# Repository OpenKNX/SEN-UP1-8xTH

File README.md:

# UP1-8xSensor
OpenKNX 8channel Temperature/Humidity Sensor

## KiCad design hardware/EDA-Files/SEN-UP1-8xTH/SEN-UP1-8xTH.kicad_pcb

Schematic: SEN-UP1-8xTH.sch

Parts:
J1: Conn_01x20; OpenKNX_UP1-PCBConnector_1x20_App_3D; LCSC C2334

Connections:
+3V3: J1.2; also elsewhere on the board
GND: J1.1; also elsewhere on the board
GPIO14: J1.5; also elsewhere on the board
GPIO15: J1.6; also elsewhere on the board
GPIO16: J1.7; also elsewhere on the board
GPIO17: J1.8; also elsewhere on the board
GPIO18: J1.9; also elsewhere on the board
GPIO19: J1.10; also elsewhere on the board
GPIO20: J1.11; also elsewhere on the board
GPIO21: J1.12; also elsewhere on the board
GPIO22: J1.13; also elsewhere on the board
GPIO23: J1.14; also elsewhere on the board
GPIO24: J1.15; also elsewhere on the board
GPIO25: J1.16; also elsewhere on the board
GPIO26: J1.17; also elsewhere on the board
GPIO27: J1.18; also elsewhere on the board
GPIO28: J1.19; also elsewhere on the board
GPIO29: J1.20; also elsewhere on the board
VCC2: J1.3

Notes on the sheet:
GP14: SPI1 SCK / UART0 CTS / I2C1 SDA / PWM7 A
GP15: SPI1 TX / UART0 RTS / I2C1 SCL / PWM7 B
GP18: SPI0 SCK / UART0 CTS / I2C1 SDA / PWM1 A
GP19: SPI0 TX / UART0 RTS / I2C1 SCL / PWM1 B
GP17: SPI0 CS / UART0 RX / I2C0 SCL / PWM0 B
GP16: SPI0 RX / UART0 TX / I2C0 SDA / PWM0 A
GP13: SPI1 CS / UART0 RX / I2C0 SCL / PWM6 B
GP20: SPI0 RX / UART1 TX / I2C0 SDA / PWM2 A
GP21: SPI0 CS / UART1 RX / I2C0 SCL / PWM2 B
GP22: SPI0 SCK / UART1 CTS / I2C1 SDA / PWM3 A
GP23: SPI0 SCK / UART1 RTS / I2C1 SCL / PWM3 B
GP24: SPI1 RX / UART1 TX / I2C0 SDA / PWM4 A
GP25: SPI1 CS / UART1 RX / I2C0 SCL / PWM4 B
GP26: SPI1 SCK / UART1 CTS / I2C1 SDA / PWM5 A / ADC0
GP27: SPI1 TX / UART1 RTS / I2C1 SCL / PWM5 B / ADC1
GP28: SPI1 RX / UART0 TX / I2C0 SDA / PWM6 A / ADC2
GP29: SPI1 CS / UART0 RX / I2C0 SCL / PWM6 B / ADC3
Vcc2 from BCU (5V)

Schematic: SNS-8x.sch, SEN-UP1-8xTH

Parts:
J2, J3: Conn_01x04; Cixi_Kefa_KF128-2.54-4p; LCSC C474922
J4, J5: Conn_01x05; Cixi_Kefa_KF128-2.54-5p
R1, R2, R3, R4, R5, R6, R7, R8, R9, R10, R11, R12, R13, R14, R15, R16: R; R_0805_2012Metric_Pad1.15x1.40mm_HandSolder
U1, U2, U3, U4, U5, U6, U7, U8: USBLC6-2SC6; SOT-23-6

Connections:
+3V3: J4.5, R1.1, R2.1, R3.1, R4.1, R5.1, R6.1, R7.1, R8.1, R9.1, R10.1, R11.1, R12.1, R13.1, R14.1, R15.1, R16.1, U1.5 (VBUS), U2.5 (VBUS), U3.5 (VBUS), U4.5 (VBUS), U5.5 (VBUS), U6.5 (VBUS), U7.5 (VBUS), U8.5 (VBUS); also elsewhere on the board
GND: J5.1, U1.2 (GND), U2.2 (GND), U3.2 (GND), U4.2 (GND), U5.2 (GND), U6.2 (GND), U7.2 (GND), U8.2 (GND); also elsewhere on the board
GPIO14: U8.3 (IO2); also elsewhere on the board
GPIO15: U8.1 (IO1); also elsewhere on the board
GPIO16: U7.3 (IO2); also elsewhere on the board
GPIO17: U7.1 (IO1); also elsewhere on the board
GPIO18: U6.3 (IO2); also elsewhere on the board
GPIO19: U6.1 (IO1); also elsewhere on the board
GPIO20: U5.3 (IO2); also elsewhere on the board
GPIO21: U5.1 (IO1); also elsewhere on the board
GPIO22: U4.3 (IO2); also elsewhere on the board
GPIO23: U4.1 (IO1); also elsewhere on the board
GPIO24: U3.3 (IO2); also elsewhere on the board
GPIO25: U3.1 (IO1); also elsewhere on the board
GPIO26: U2.3 (IO2); also elsewhere on the board
GPIO27: U2.1 (IO1); also elsewhere on the board
GPIO28: U1.3 (IO2); also elsewhere on the board
GPIO29: U1.1 (IO1); also elsewhere on the board
SCL0_A_P: J2.1, R16.2, U1.6 (IO1)
SCL0_C_P: J4.1, R12.2, U3.6 (IO1)
SCL0_E_P: J5.2, R8.2, U5.6 (IO1)
SCL0_G_P: J3.1, R4.2, U7.6 (IO1)
SCL1_B_P: J2.3, R14.2, U2.6 (IO1)
SCL1_D_P: J4.3, R10.2, U4.6 (IO1)
SCL1_F_P: J5.4, R6.2, U6.6 (IO1)
SCL1_H_P: J3.3, R2.2, U8.6 (IO1)
SDA0_A_P: J2.2, R15.2, U1.4 (IO2)
SDA0_C_P: J4.2, R11.2, U3.4 (IO2)
SDA0_E_P: J5.3, R7.2, U5.4 (IO2)
SDA0_G_P: J3.2, R3.2, U7.4 (IO2)
SDA1_B_P: J2.4, R13.2, U2.4 (IO2)
SDA1_D_P: J4.4, R9.2, U4.4 (IO2)
SDA1_F_P: J5.5, R5.2, U6.4 (IO2)
SDA1_H_P: J3.4, R1.2, U8.4 (IO2)

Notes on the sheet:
Sensor (SHT31, BME280, ...)

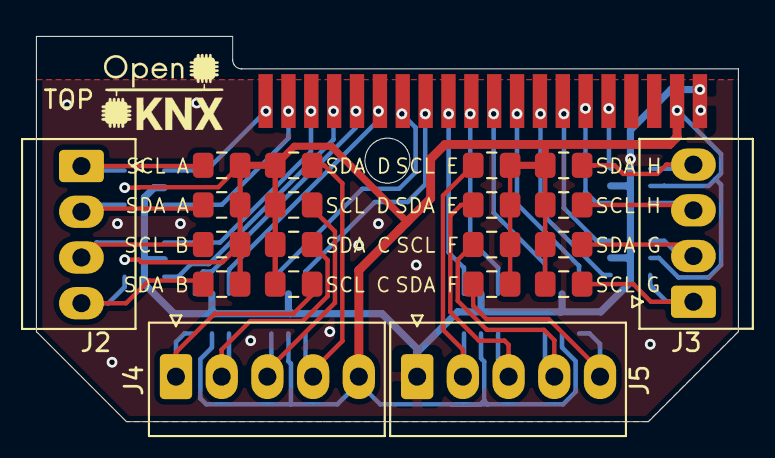
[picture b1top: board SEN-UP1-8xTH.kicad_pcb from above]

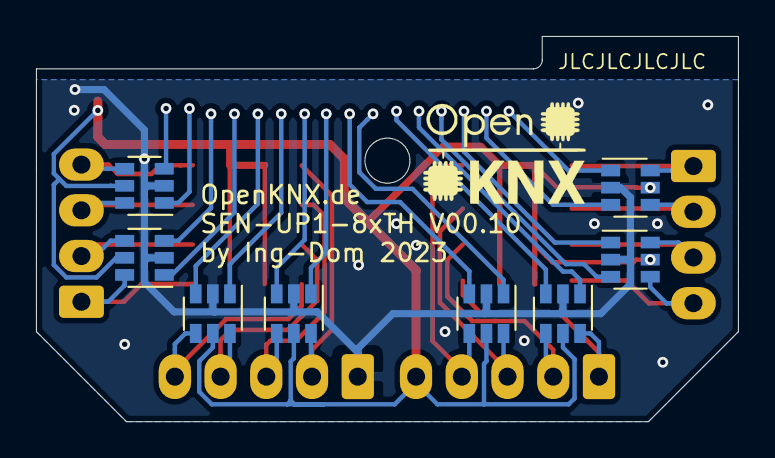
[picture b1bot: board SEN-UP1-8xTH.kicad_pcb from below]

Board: 2 copper layers, 39.0 x 21.4 mm, 29 parts (8 on the bottom side), 34 nets.

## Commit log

2022-02-16 V00.02
2022-02-17 added small pic
2022-10-13 added 3D construction data for case
2023-01-28 SEN-UP1-8xTH_V00.10
2023-02-20 added docu
2023-02-20 add 003 case
2023-02-20 added 003 case
2023-02-25 initial version of device FW / device xml
2023-03-05 SEN-UP1-8xTH.knxprod Dev 0.2
2023-03-05 SEN-UP1-8xTH.knxprod Dev 0.3
2023-03-05 SEN-UP1-8xTH.knxprod Dev 0.4
2023-03-05 SEN-UP1-8xTH.knxprod Dev 0.5
2023-03-05 knxprod Dev 0.6
2023-03-06 knxprod Dev 0.8
2023-03-06 added channel numbering
2023-03-06 knxprod dev 0.9
2023-04-03 changed to OFM-LogicModule
2023-05-30 adapted to new common knxprod and fw builds not tested
2023-05-30 added baggages dir
2023-06-02 update to new platform example
2023-06-02 fix: add missing loop1
2023-06-04 update platformio
2023-06-04 update dep
2023-06-15 added Updater
2023-06-20 working build with update
2023-07-04 switch to knx devel
2023-09-29 builds
2023-09-29 debug hang on startup
2023-10-01 info led on unused Pin 13
2023-10-04 added BTN Module Version check
2023-10-08 latest common
2023-10-23 switch to OFM versioning using library.json, increased App-Version
2023-10-24 release prep
2023-10-24 new scripts from common, corrected release definition in ini added Release.xml
2023-10-24 adding Release / Beta Release tasks
2023-10-24 switch to main branch of THP Module
2023-10-24 0.1.0-release
2023-10-24 fix name
2023-10-27 increase revision
2023-10-27 release V0.1.1
2023-10-30 added KiCAD project
2023-10-30 ignore
2023-11-03 case variant without Screwholes (normally not neccessary)
2024-01-27 docu
2024-01-28 adaption to v1 / producer 3
2024-02-17 wip, builds but crashes on startup
2024-02-17 fix crash
2024-02-18 Prepare Release V0.2
2025-01-24 - addded ConfigTransfer - newest OpenKNX Common/Logic etc...
2025-01-24 fix pio envs
2025-01-24 change to HardwareConfig
2025-01-25 prepare Beta 1.14 / Release 1.0
2025-01-26 V1.4.1-Beta, include THPSensorModule 0.3.1
2025-12-18 wip adapt to common 1.5
2025-12-18 rename xml to Dev
2025-12-18 Dev-Release v1.5.0
2026-01-30 V1.7-Dev, last refinements
2026-02-24 updated to common 1.7
2026-02-24 Dev-1.9.0
2026-02-27 v1.0.0 v1.10.0-Dev
